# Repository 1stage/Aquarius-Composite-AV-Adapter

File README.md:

# Composite-AV-Adapter

Quick Note: There are two versions of this board. The easier one to build (v1.1 or 02, 20 SEP 2019) is the DIY through-hole version. The SMD (v2.0 or 04, 10 DEC 2019) version is smaller, but requires surface-mount components. Functionally, they are identical.

For BOTH versions, this is the correct AV cable to use: https://www.amazon.com/dp/B06XKMBB9L

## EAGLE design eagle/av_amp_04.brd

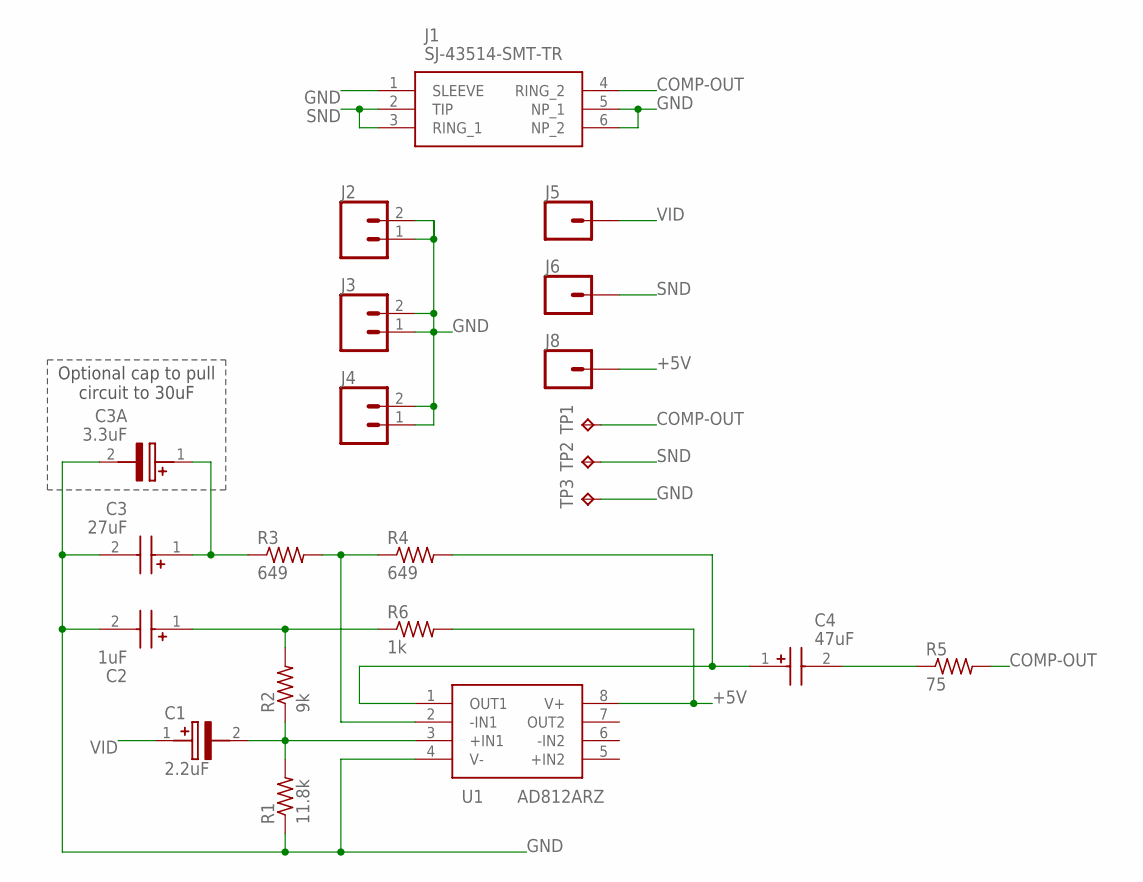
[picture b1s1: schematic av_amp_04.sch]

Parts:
C1: 2.2uF; CAPAE430X550N
C2: 1uF; CAPAE430X565N
C3: 27uF; 865080342004
C3A: 3.3uF; 865080540001
C4: 47uF; EDK(5X5.4)
J1: SJ-43514-SMT-TR
J2, J3, J4: CONN_02; 1X02
J5, J6, J8: CONN_01; 1X01
R1: 11.8k; R0603
R2: 9k; R0603
R3, R4: 649; R0603
R5: 75; R0603
R6: 1k; R0603
TP1, TP2, TP3: TPB2,54; B2,54
U1: AD812ARZ; SOIC127P600X175-8N

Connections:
+5V: J8.1, R6.2, U1.8 (V+)
COMP-OUT: J1.4 (RING_2), R5.2, TP1.TP
GND: C2.2 (-), C3.2 (+), C3A.2 (-), J1.1 (SLEEVE), J1.5 (NP_1), J1.6 (NP_2), J2.1, J2.2, J3.1, J3.2, J4.1, J4.2, R1.1, TP3.TP, U1.4 (V-)
unnamed: C3.1 (-), C3A.1 (+), R3.1
unnamed: R3.2, R4.1, U1.2 (-IN1)
unnamed: C1.2 (-), R1.2, R2.1, U1.3 (+IN1)
unnamed: C4.1 (+), R4.2, U1.1 (OUT1)
unnamed: C4.2 (-), R5.1
unnamed: C2.1 (+), R2.2, R6.1
SND: J1.2 (TIP), J1.3 (RING_1), J6.1, TP2.TP
VID: C1.1 (+), J5.1

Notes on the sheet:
Optional cap to pull circuit to 30uF

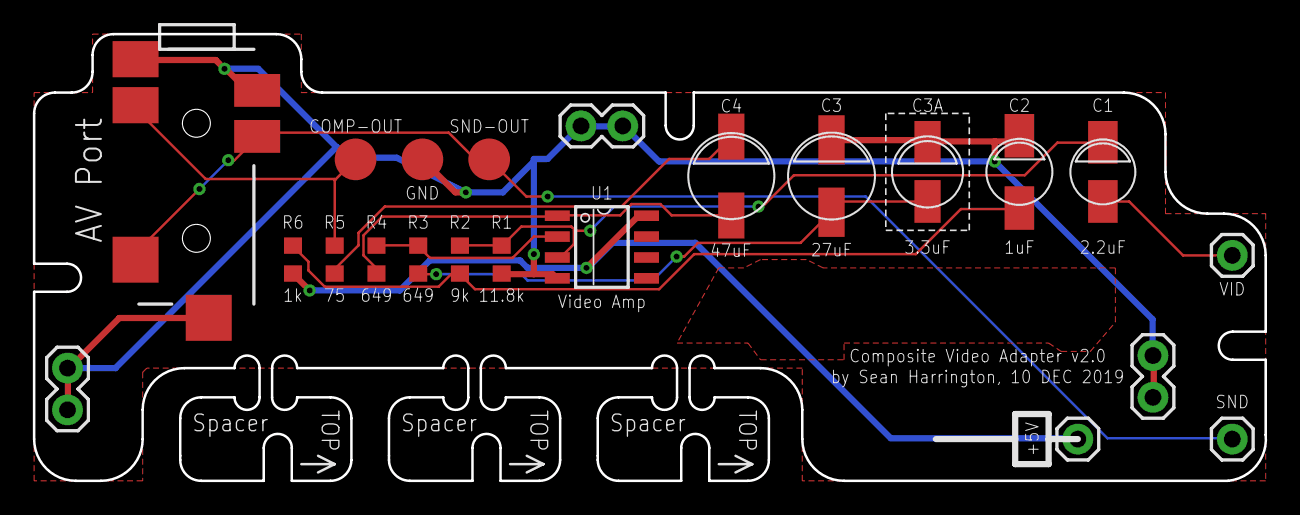
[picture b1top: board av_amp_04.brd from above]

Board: 2 copper layers, 74.9 x 27.2 mm, 22 parts (0 on the bottom side), 11 nets.

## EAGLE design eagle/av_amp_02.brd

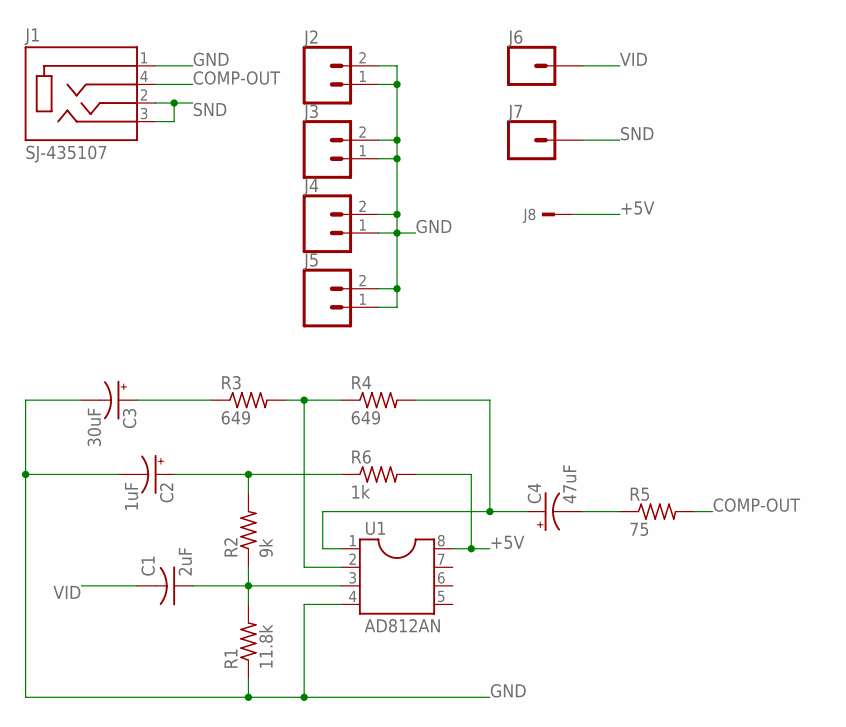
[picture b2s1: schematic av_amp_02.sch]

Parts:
C1: 2uF; C225-087X268
C2: 1uF; E5-5
C3: 30uF; E5-10,5
C4: 47uF; E5-6
J1: SJ-435107; CUI_SJ-435107
J2, J3, J4, J5: CONN_02; 1X02
J6, J7: CONN_01; 1X01
J8: TSW-101-08-G-S-S-RA; TSW-101-08-G-S-RA
R1: 11.8k; 0207/10
R2: 9k; 0207/10
R3, R4: 649; 0207/10
R5: 75; 0207/10
R6: 1k; 0207/10
U1: AD812AN; DIL08

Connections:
+5V: J8.1, R6.2, U1.8
COMP-OUT: J1.4 (RING2), R5.2
GND: C2.-, C3.-, J1.1 (SLEEVE), J2.1, J2.2, J3.1, J3.2, J4.1, J4.2, J5.1, J5.2, R1.1, U1.4
unnamed: C3.+, R3.1
unnamed: R3.2, R4.1, U1.2
unnamed: C1.1, R1.2, R2.1, U1.3
unnamed: C4.+, R4.2, U1.1
unnamed: C4.-, R5.1
unnamed: C2.+, R2.2, R6.1
SND: J1.2 (TIP), J1.3 (RING1), J7.1
VID: C1.2, J6.1

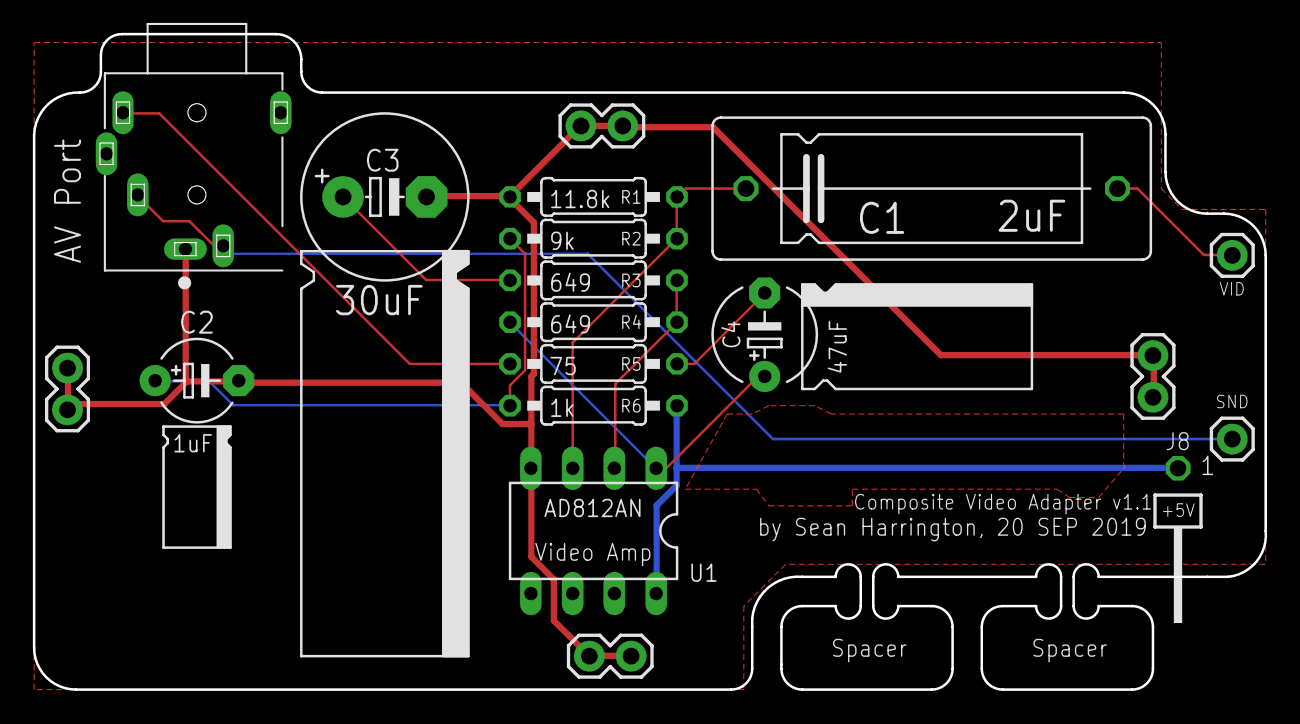
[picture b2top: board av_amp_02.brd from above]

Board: 2 copper layers, 74.9 x 39.9 mm, 19 parts (0 on the bottom side), 11 nets.

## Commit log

2020-10-06 Adding first sets of files
2020-10-07 Added images and documentation for ebay listing.
2021-08-11 Moving to open source clean-up

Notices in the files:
parts and their libraries:
SparkFun-Connectors: Licensing: Creative Commons ShareAlike 4.0 International - https://creativecommons.org/licenses/by-sa/4.0
